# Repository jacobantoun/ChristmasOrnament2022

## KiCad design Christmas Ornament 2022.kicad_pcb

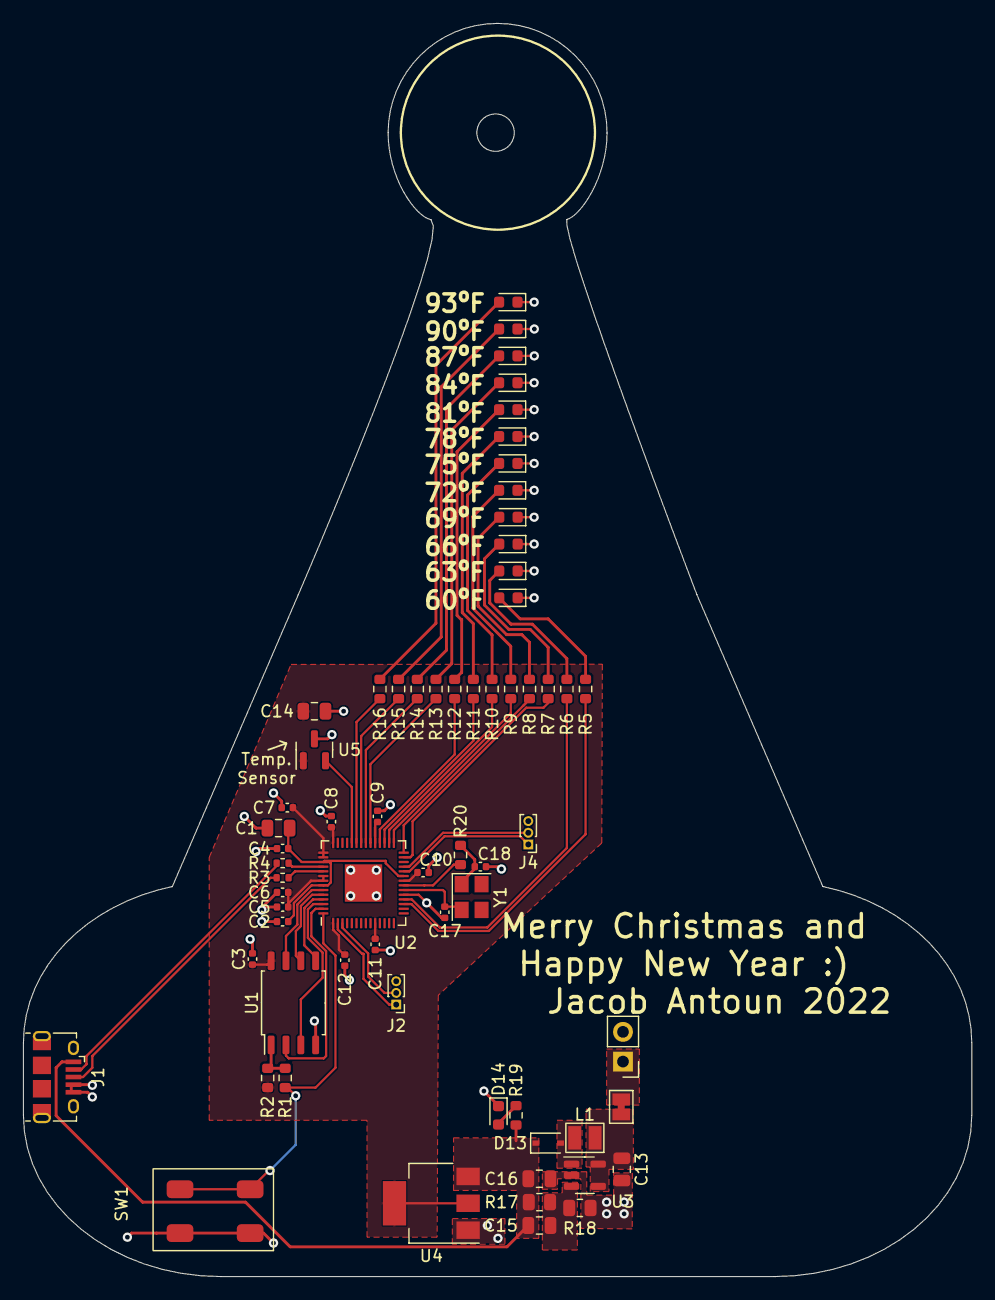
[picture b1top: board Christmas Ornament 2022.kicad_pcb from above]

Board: 2 copper layers, 81.1 x 107.2 mm, 66 parts (0 on the bottom side), 52 nets.

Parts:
C1, C14, C16: 1u; C_0805_2012Metric
C2, C3, C4, C5, C6, C7, C8, C9, C10, C11, C12: 100n; C_0402_1005Metric
C13: 4.7u; C_0805_2012Metric
C15: 22p; C_0805_2012Metric
C17, C18: 30p; C_0402_1005Metric
D1, D2, D3: Blue LED; LED_0603_1608Metric
D4, D5, D6: Green LED; LED_0603_1608Metric
D7, D8, D9: Yellow LED; LED_0603_1608Metric
D10, D11, D12: Red LED; LED_0603_1608Metric
D13: D_Schottky_Small; D_SOD-323
D14: Green PWR LED; LED_0603_1608Metric
H1: MountingHole; MountingHole_3.2mm_M3
J1: USB_B_Micro; USB_Micro-B_Amphenol_10118194_Horizontal
J2, J4: Conn_01x03; PinHeader_1x03_P1.00mm_Vertical
J3: Battery Input; PinHeader_1x02_P2.54mm_Vertical
JP1: Jumper_2_Bridged; SolderJumper-2_P1.3mm_Bridged_Pad1.0x1.5mm
L1: 10u; CKCS252010
R1, R20: 1.1k; R_0603_1608Metric
R2: 10k; R_0603_1608Metric
R3, R4: 27.4; R_0402_1005Metric
R5, R6, R7: 20; R_0603_1608Metric
R8, R9, R10, R11, R12, R13: 75; R_0603_1608Metric
R14, R15, R16: 100; R_0603_1608Metric
R17: 249k; R_0805_2012Metric
R18: 150k; R_0805_2012Metric
R19: 180; R_0603_1608Metric
SW1: SW_Push; TS-1187A-B-A-B
U1: W25Q32JVSS; SOIC-8_5.23x5.23mm_P1.27mm
U2: RP2040; QFN-56-1EP_7x7mm_P0.4mm_EP3.2x3.2mm
U3: TPS61040DBV; SOT-23-5
U4: AMS1117-3.3; SOT-223-3_TabPin2
U5: MCP9700T-ETT; SOT-23
Y1: 12MHz; Crystal_SMD_3225-4Pin_3.2x2.5mm

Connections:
+1V1: C1.1, C2.1, C4.1, U2.23 (DVDD), U2.45 (VREG_VOUT), U2.50 (DVDD)
+3.3V: C3.1, C5.1, C6.1, C7.1, C8.1, C9.1, C10.1, C11.1, C12.1, C14.1, R2.2, U1.8 (VCC), U2.1 (IOVDD), U2.10 (IOVDD), U2.22 (IOVDD), U2.33 (IOVDD), U2.42 (IOVDD), U2.43 (ADC_AVDD), U2.44 (VREG_IN), U2.48 (USB_VDD), U2.49 (IOVDD), U4.2 (VO), U5.1 (Vdd)
+5V: C15.1, C16.1, D13.1 (K), J1.1 (VBUS), R17.1, R19.2, U4.3 (VI)
+BATT: J3.1, JP1.1 (A)
/DBG_SWCLK: J4.1, U2.24 (SWCLK)
/DBG_SWD: J4.2, U2.25 (SWD)
/QSPI_SCLK: U1.6 (CLK), U2.52 (QSPI_SCLK)
/QSPI_SD0: U1.5 (DI(IO0)), U2.53 (QSPI_SD0)
/QSPI_SD1: U1.2 (DO(IO1)), U2.55 (QSPI_SD1)
/QSPI_SD2: U1.3 (IO2), U2.54 (QSPI_SD2)
/QSPI_SD3: U1.7 (IO3), U2.51 (QSPI_SD3)
/QSPI_SS: R1.1, SW1.2, U2.56 (QSPI_SS)
/RP2040_XIN: C17.2, U2.20 (XIN), Y1.2
/RP2040_XOUT: R20.2, U2.21 (XOUT)
GND: C1.2, C2.2, C3.2, C4.2, C5.2, C6.2, C7.2, C8.2, C9.2, C10.2, C11.2, C12.2, C13.2, C14.2, C16.2, C17.1, C18.1, D1.1 (K), D2.1 (K), D3.1 (K), D4.1 (K), D5.1 (K), D6.1 (K), D7.1 (K), D8.1 (K), D9.1 (K), D10.1 (K), D11.1 (K), D12.1 (K), D14.1 (K), J1.4 (ID), J1.5 (GND), J2.3, J3.2, J4.3, R18.2, SW1.1, U1.4 (GND), U2.19 (TESTEN), U2.57 (GND), U3.2 (GND), U4.1 (GND), U5.3 (GND)
LED1: R5.1, U2.17 (GPIO14)
LED2: R6.1, U2.18 (GPIO15)
LED3: R7.1, U2.27 (GPIO16)
LED4: R8.1, U2.28 (GPIO17)
LED5: R9.1, U2.29 (GPIO18)
LED6: R10.1, U2.30 (GPIO19)
LED7: R11.1, U2.31 (GPIO20)
LED8: R12.1, U2.32 (GPIO21)
LED9: R13.1, U2.34 (GPIO22)
LED10: R14.1, U2.35 (GPIO23)
LED11: R15.1, U2.36 (GPIO24)
LED12: R16.1, U2.37 (GPIO25)
MCP9700_AOUT: U2.38 (GPIO26_ADC0), U5.2 (Vout)
unnamed: C13.1, JP1.2 (B), L1.1, U3.4 (EN), U3.5 (VIN)
unnamed: C15.2, R17.2, R18.1, U3.3 (FB)
unnamed: C18.2, R20.1, Y1.1
unnamed: D1.2 (A), R5.2
unnamed: D2.2 (A), R6.2
unnamed: D3.2 (A), R7.2
unnamed: D4.2 (A), R8.2
unnamed: D5.2 (A), R9.2
unnamed: D6.2 (A), R10.2
unnamed: D7.2 (A), R11.2
unnamed: D8.2 (A), R12.2
unnamed: D9.2 (A), R13.2
unnamed: D10.2 (A), R14.2
unnamed: D11.2 (A), R15.2
unnamed: D12.2 (A), R16.2
unnamed: D13.2 (A), L1.2, U3.1 (SW)
unnamed: D14.2 (A), R19.1
unnamed: R1.2, R2.1, U1.1 (~CS)
unnamed: R3.1, U2.47 (USB_DP)
unnamed: R4.1, U2.46 (USB_DM)
UART0_RX: J2.2, U2.3 (GPIO1)
UART0_TX: J2.1, U2.2 (GPIO0)
USB_D+: J1.3 (D+), R3.2
USB_D-: J1.2 (D-), R4.2

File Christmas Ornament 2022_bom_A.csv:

Component,Description,Part,References,Value,Footprint,Quantity Per PCB,Datasheet,Part Number,Vendor
1,"Unpolarized capacitor, small symbol",C_Small,C2 C3 C4 C5 C6 C7 C8 C9 C10 C11 C12,100n,C_0805_2012Metric,11,~,C49678,JLCPCB
2,"Unpolarized capacitor, small symbol",C_Small,C1 C14 C16,1u,C_0805_2012Metric,3,~,C28323,JLCPCB
3,"Unpolarized capacitor, small symbol",C_Small,C15,22p,C_0805_2012Metric,1,~,C1804,JLCPCB
4,"Unpolarized capacitor, small symbol",C_Small,C13,4.7u,C_0805_2012Metric,1,~,C1779,JLCPCB
5,"Light emitting diode, small symbol, filled shape",LED_Small_Filled,D1 D2 D3,Blue LED,LED_0603_1608Metric,3,~,C72041,JLCPCB
6,"Schottky diode, small symbol",D_Schottky_Small,D13,D_Schottky_Small,D_SOD-323,1,~,C191023,JLCPCB
7,"Light emitting diode, small symbol, filled shape",LED_Small_Filled,D4 D5 D6,Green LED,LED_0603_1608Metric,3,~,C72043,JLCPCB
8,"Light emitting diode, small symbol, filled shape",LED_Small_Filled,D10 D11 D12,Red LED,LED_0603_1608Metric,3,~,C2286,JLCPCB
9,"Light emitting diode, small symbol, filled shape",LED_Small_Filled,D7 D8 D9,Yellow LED,LED_0603_1608Metric,3,~,C72038,JLCPCB
10,USB Micro Type B connector,USB_B_Micro,J1,USB_B_Micro,USB_Micro-B_Amphenol_10118194_Horizontal,1,~,C132563,JLCPCB
11,"Jumper, 2-pole, closed/bridged",Jumper_2_Bridged,JP1,Jumper_2_Bridged,SolderJumper-2_P1.3mm_Bridged_Pad1.0x1.5mm,1,~,,
12,"Inductor, small symbol",L_Small,L1,10u,CKCS252010,1,~,C354548,JLCPCB
13,"Resistor, small symbol",R_Small,R1,1.1k,R_0603_1608Metric,1,~,C22764,JLCPCB
14,"Resistor, small symbol",R_Small,R14 R15 R16,100,R_0603_1608Metric,3,~,C22775,JLCPCB
15,"Resistor, small symbol",R_Small,R2,10k,R_0603_1608Metric,1,~,C25804,JLCPCB
16,"Resistor, small symbol",R_Small,R18,150k,R_0805_2012Metric,1,~,C17470,JLCPCB
17,"Resistor, small symbol",R_Small,R5 R6 R7,20,R_0603_1608Metric,3,~,C22950,JLCPCB
18,"Resistor, small symbol",R_Small,R17,249k,R_0805_2012Metric,1,~,C25825,JLCPCB
19,"Resistor, small symbol",R_Small,R3 R4,27.4,R_0402_1005Metric,2,~,C172043,JLCPCB
20,"Resistor, small symbol",R_Small,R8 R9 R10 R11 R12 R13,75,R_0603_1608Metric,6,~,C4275,JLCPCB
21,"Push button switch, generic, two pins",SW_Push,SW1,SW_Push,TS-1187A-B-A-B,1,~,C318884,JLCPCB
22,"1A Low Dropout regulator, positive, 3.3V fixed output, SOT-223",AMS1117-3.3,U4,AMS1117-3.3,SOT-223-3_TabPin2,1,http://www.advanced-monolithic.com/pdf/ds1117.pdf,C6186,JLCPCB
23,"Low power, analog thermistor temperature sensor, ±4C accuracy, -40C to +125C, in SOT-23-3",MCP9700T-ETT,U5,MCP9700T-ETT,SOT-23,1,http://ww1.microchip.com/downloads/en/DeviceDoc/21942e.pdf,C127949,JLCPCB
24,A microcontroller by Raspberry Pi,RP2040,U2,RP2040,QFN-56-1EP_7x7mm_P0.4mm_EP3.2x3.2mm,1,https://datasheets.raspberrypi.com/rp2040/rp2040-datasheet.pdf,C2040,JLCPCB
25,"Synchronous Boost Regulator, Adjustable Output up to 28V, 400 mA Switch Current Limit, SOT-23-5",TPS61040DBV,U3,TPS61040DBV,SOT-23-5,1,http://www.ti.com/lit/ds/symlink/tps61040.pdf,C7722,JLCPCB
26,"32Mb Serial Flash Memory, Standard/Dual/Quad SPI, SOIC-8",W25Q32JVSS,U1,W25Q32JVSS,SOIC-8_5.23x5.23mm_P1.27mm,1,http://www.winbond.com/resource-files/w25q32jv%20revg%200327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,C2980995,JLCPCB





Component Groups:,26
Component Count:,56
Fitted Components:,56
Number of PCBs:,1
Total components:,56
Schematic Version:,A
Schematic Date:,2022-12-08
PCB Variant:,default
BoM Date:,12/8/2022 6:10:29 PM
Schematic Source:,C:\Users\jantoun\Documents\ChristmasOrnament2022\Christmas Ornament 2022.kicad_sch
KiCad Version:,Eeschema (6.0.8)

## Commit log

2022-12-08 Added flash and connected IO
2022-12-11 Finished layout
